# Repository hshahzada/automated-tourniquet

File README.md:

View this project on [CADLAB.io](https://cadlab.io/project/27395). 

# automated-tourniquet
2023/2024 Capstone Design Project for Biomedical Engineering

Created by:

Diana Temelkos dtemelkos@torontomu.ca
https://www.linkedin.com/in/dianatemelkos/

Hassan Khan hassan.a.khan@torontomu.ca
https://www.linkedin.com/in/hassan-khan-5604501a9/

Haashim Shahzada hshahzada@torontomu.ca
https://www.linkedin.com/in/haashimshahzada/

Sayeed Hasan sayeed.hasan@torontomu.ca
https://www.linkedin.com/in/sayeedhasanli/

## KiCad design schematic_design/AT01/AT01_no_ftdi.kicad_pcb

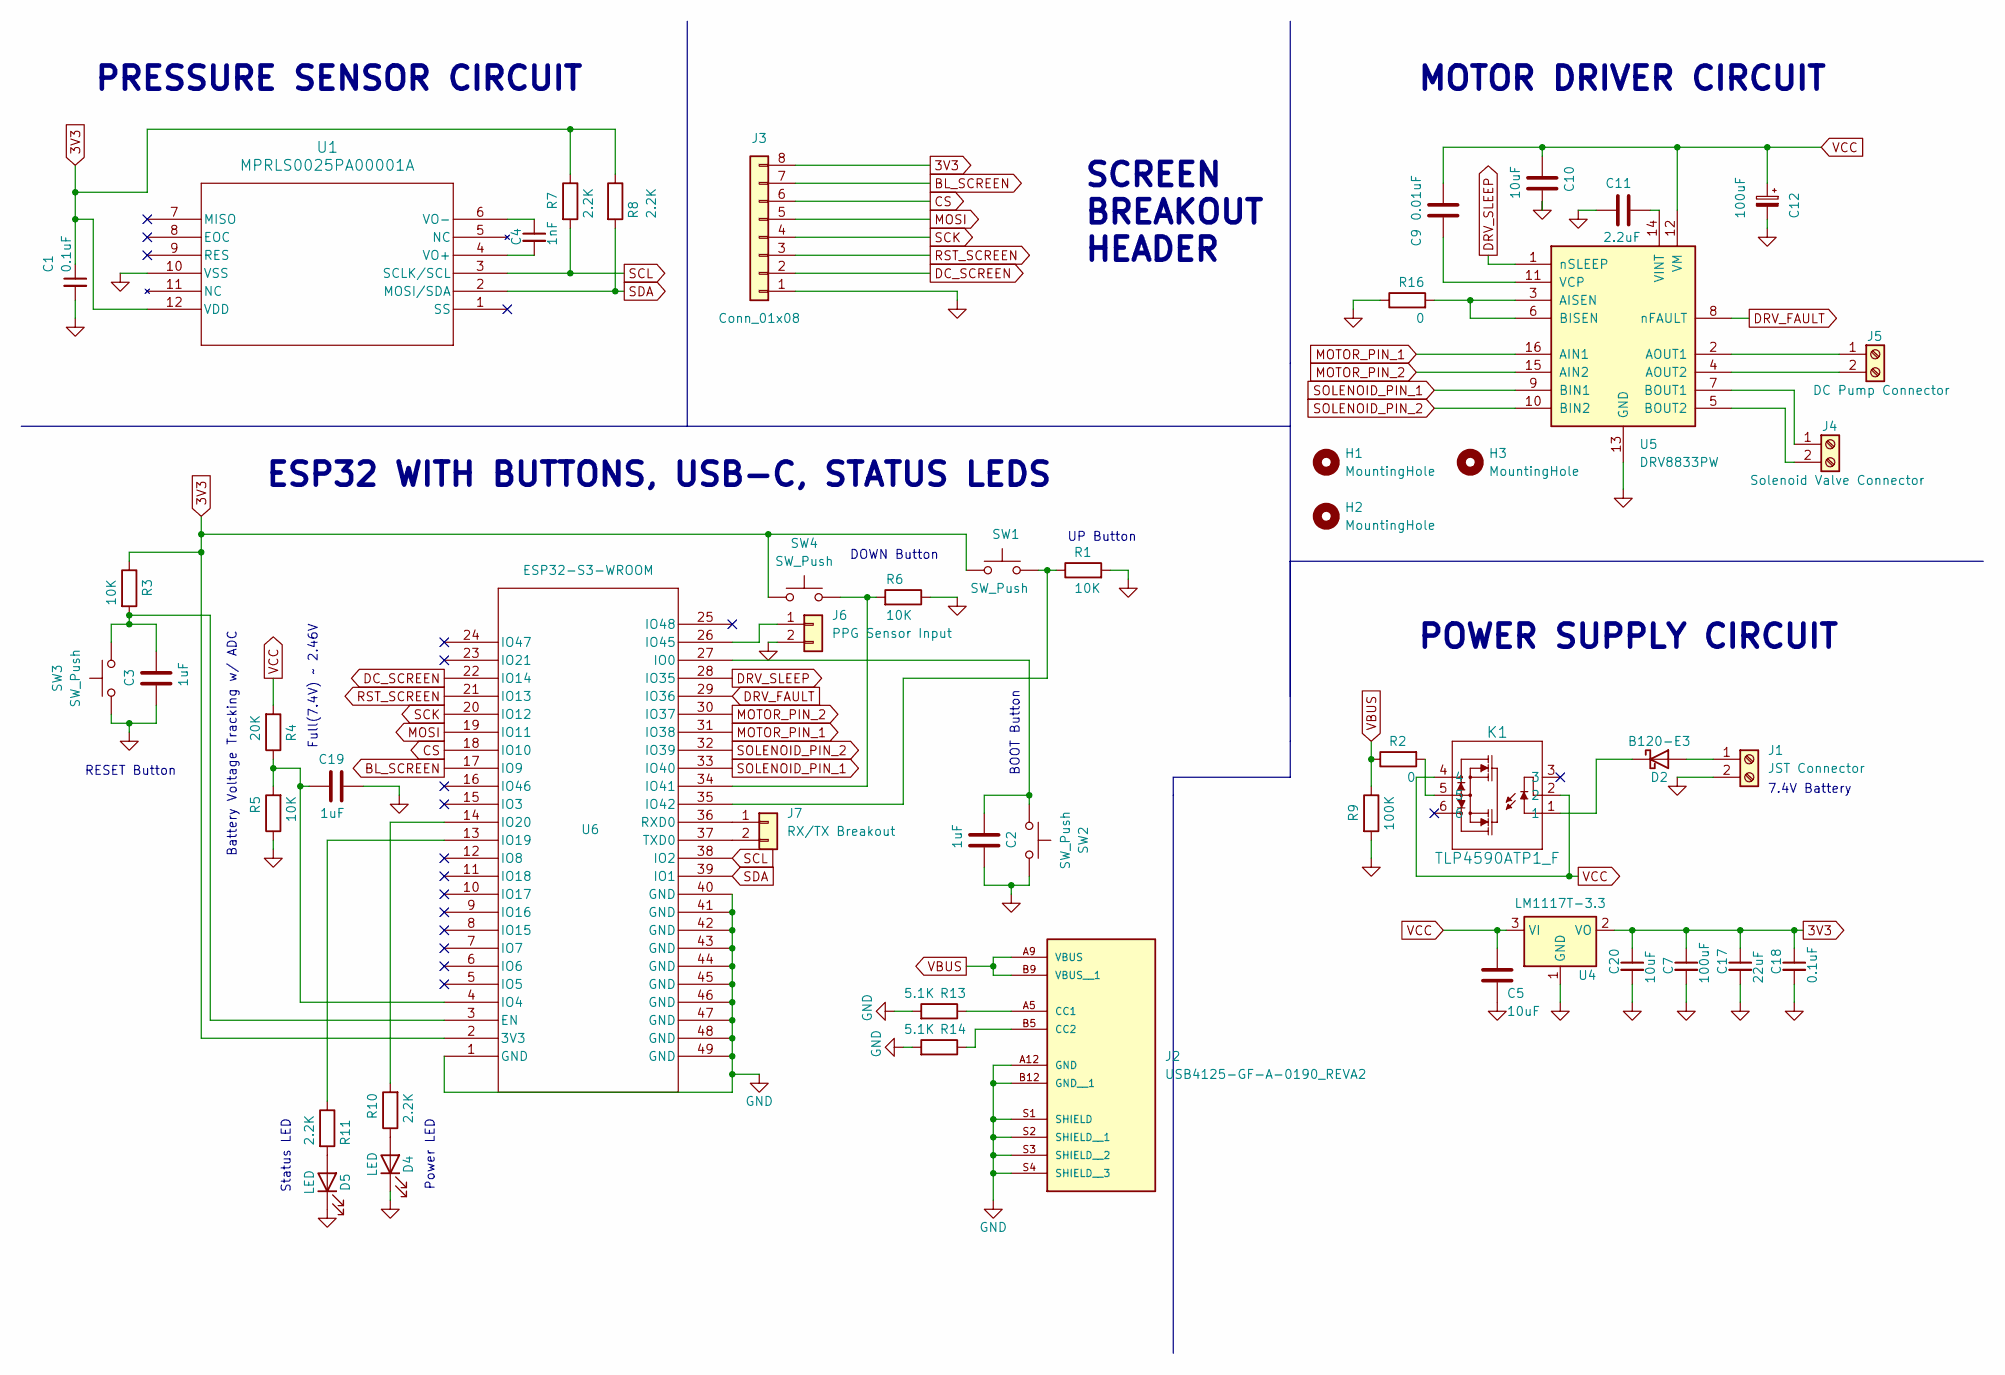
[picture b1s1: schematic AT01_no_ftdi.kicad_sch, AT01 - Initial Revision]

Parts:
C1, C18: 0.1uF; C_0603_1608Metric_Pad1.08x0.95mm_HandSolder
C2, C3, C19: 1uF; C_0603_1608Metric_Pad1.08x0.95mm_HandSolder
C4: 1nF; C_0603_1608Metric_Pad1.08x0.95mm_HandSolder
C5, C10, C20: 10uF; C_0603_1608Metric_Pad1.08x0.95mm_HandSolder
C7: 100uF; C_0805_2012Metric_Pad1.18x1.45mm_HandSolder
C9: 0.01uF; C_0603_1608Metric_Pad1.08x0.95mm_HandSolder
C11: 2.2uF; C_0603_1608Metric_Pad1.08x0.95mm_HandSolder
C12: 100uF; CP_Elec_6.3x5.2
C17: 22uF; C_0603_1608Metric_Pad1.08x0.95mm_HandSolder
D2: B120-E3; D_SMA
D4, D5: LED; LED_D3.0mm
H1, H2, H3: MountingHole; MountingHole_2.2mm_M2_ISO7380
J1: JST Connector; JST_EH_S2B-EH_1x02_P2.50mm_Horizontal
J2: USB4125-GF-A-0190_REVA2; GCT_USB4125-GF-A-0190_REVA2; PARTREV Rev A2
J3: Conn_01x08; PinHeader_1x08_P2.54mm_Vertical
J4: Solenoid Valve Connector; TerminalBlock_4Ucon_1x02_P3.50mm_Horizontal
J5: DC Pump Connector; TerminalBlock_4Ucon_1x02_P3.50mm_Horizontal
J6: PPG Sensor Input; PinHeader_1x02_P2.54mm_Vertical
J7: RX/TX Breakout; PinHeader_1x02_P2.54mm_Vertical
K1: TLP4590ATP1_F; 11-7A801S_TOS
R1, R3, R5, R6: 10K; R_0603_1608Metric_Pad0.98x0.95mm_HandSolder
R2, R16: 0; R_0603_1608Metric_Pad0.98x0.95mm_HandSolder
R4: 20K; R_0603_1608Metric_Pad0.98x0.95mm_HandSolder
R7, R8, R10, R11: 2.2K; R_0603_1608Metric_Pad0.98x0.95mm_HandSolder
R9: 100K; R_0603_1608Metric_Pad0.98x0.95mm_HandSolder
R13, R14: 5.1K; R_0603_1608Metric_Pad0.98x0.95mm_HandSolder
SW1, SW2, SW3, SW4: SW_Push; SW_PUSH_6mm
U1: MPRLS0025PA00001A; MPRLS_HNW
U4: LM1117T-3.3; TO-220-3_Horizontal_TabDown
U5: DRV8833PW; TSSOP-16_4.4x5mm_P0.65mm
U6: ESP32-S3-WROOM; ESP32-S3-WROOM-1U

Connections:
3V3: C1.1, C7.1, C17.1, C18.1, C20.1, J3.8, R3.1, R7.1, R8.1, SW1.1, SW4.1, U1.12 (VDD), U4.2 (VO), U6.2 (3V3)
BL_SCREEN: J3.7, U6.17 (IO9)
CS: J3.6, U6.18 (IO10)
DC_SCREEN: J3.2, U6.22 (IO14)
DRV_FAULT: U5.8 (nFAULT), U6.29 (IO36)
DRV_SLEEP: U5.1 (nSLEEP), U6.28 (IO35)
GND: C1.2, C2.2, C3.2, C5.2, C7.2, C10.1, C11.1, C12.2, C17.2, C18.2, C19.2, C20.2, D4.1 (K), D5.1 (K), J1.2, J2.A12 (GND), J2.B12 (GND__1), J2.S1 (SHIELD), J2.S2 (SHIELD__1), J2.S3 (SHIELD__2), J2.S4 (SHIELD__3), J3.1, J6.2, R1.2, R5.1, R6.1, R9.2, R13.2, R14.2, R16.1, SW2.2, SW3.2, U1.10 (VSS), U4.1 (GND), U5.13 (GND), U6.1 (GND), U6.40 (GND), U6.41 (GND), U6.42 (GND), U6.43 (GND), U6.44 (GND), U6.45 (GND), U6.46 (GND), U6.47 (GND), U6.48 (GND), U6.49 (GND)
MOSI: J3.5, U6.19 (IO11)
MOTOR_PIN_1: U5.16 (AIN1), U6.31 (IO38)
MOTOR_PIN_2: U5.15 (AIN2), U6.30 (IO37)
unnamed: D2.2 (A), J1.1
unnamed: D2.1 (K), K1.1
unnamed: D4.2 (A), R10.1
unnamed: D5.2 (A), R11.2
unnamed: J2.A5 (CC1), R13.1
unnamed: J2.B5 (CC2), R14.1
unnamed: J4.1, U5.7 (BOUT1)
unnamed: J4.2, U5.5 (BOUT2)
unnamed: J5.1, U5.2 (AOUT1)
unnamed: J5.2, U5.4 (AOUT2)
unnamed: J6.1, U6.26 (IO45)
unnamed: J7.1, U6.36 (RXD0)
unnamed: J7.2, U6.37 (TXD0)
unnamed: K1.5, R2.2
unnamed: C4.2, U1.4 (VO+)
unnamed: C4.1, U1.6 (VO-)
unnamed: R16.2, U5.3 (AISEN), U5.6 (BISEN)
unnamed: C9.1, U5.11 (VCP)
unnamed: C11.2, U5.14 (VINT)
unnamed: C3.1, R3.2, SW3.1, U6.3 (EN)
unnamed: C2.1, SW2.1, U6.27 (IO0)
unnamed: C19.1, R4.1, R5.2, U6.4 (IO4)
unnamed: R11.1, U6.13 (IO19)
unnamed: R10.2, U6.14 (IO20)
unnamed: R6.2, SW4.2, U6.34 (IO41)
unnamed: R1.1, SW1.2, U6.35 (IO42)
RST_SCREEN: J3.3, U6.21 (IO13)
SCK: J3.4, U6.20 (IO12)
SCL: R7.2, U1.3 (SCLK/SCL), U6.38 (IO2)
SDA: R8.2, U1.2 (MOSI/SDA), U6.39 (IO1)
SOLENOID_PIN_1: U5.9 (BIN1), U6.33 (IO40)
SOLENOID_PIN_2: U5.10 (BIN2), U6.32 (IO39)
VBUS: J2.A9 (VBUS), J2.B9 (VBUS__1), R2.1, R9.1
VCC: C5.1, C9.2, C10.2, C12.1, K1.2, K1.4, R4.2, U4.3 (VI), U5.12 (VM)

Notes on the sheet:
UP Button
Full(7.4V) ~ 2.46V
PRESSURE SENSOR CIRCUIT
RESET Button
POWER SUPPLY CIRCUIT
7.4V Battery
ESP32 WITH BUTTONS, USB-C, STATUS LEDS
Power LED
SCREEN BREAKOUT HEADER
BOOT Button
MOTOR DRIVER CIRCUIT
DOWN Button
Battery Voltage Tracking w/ ADC
Status LED

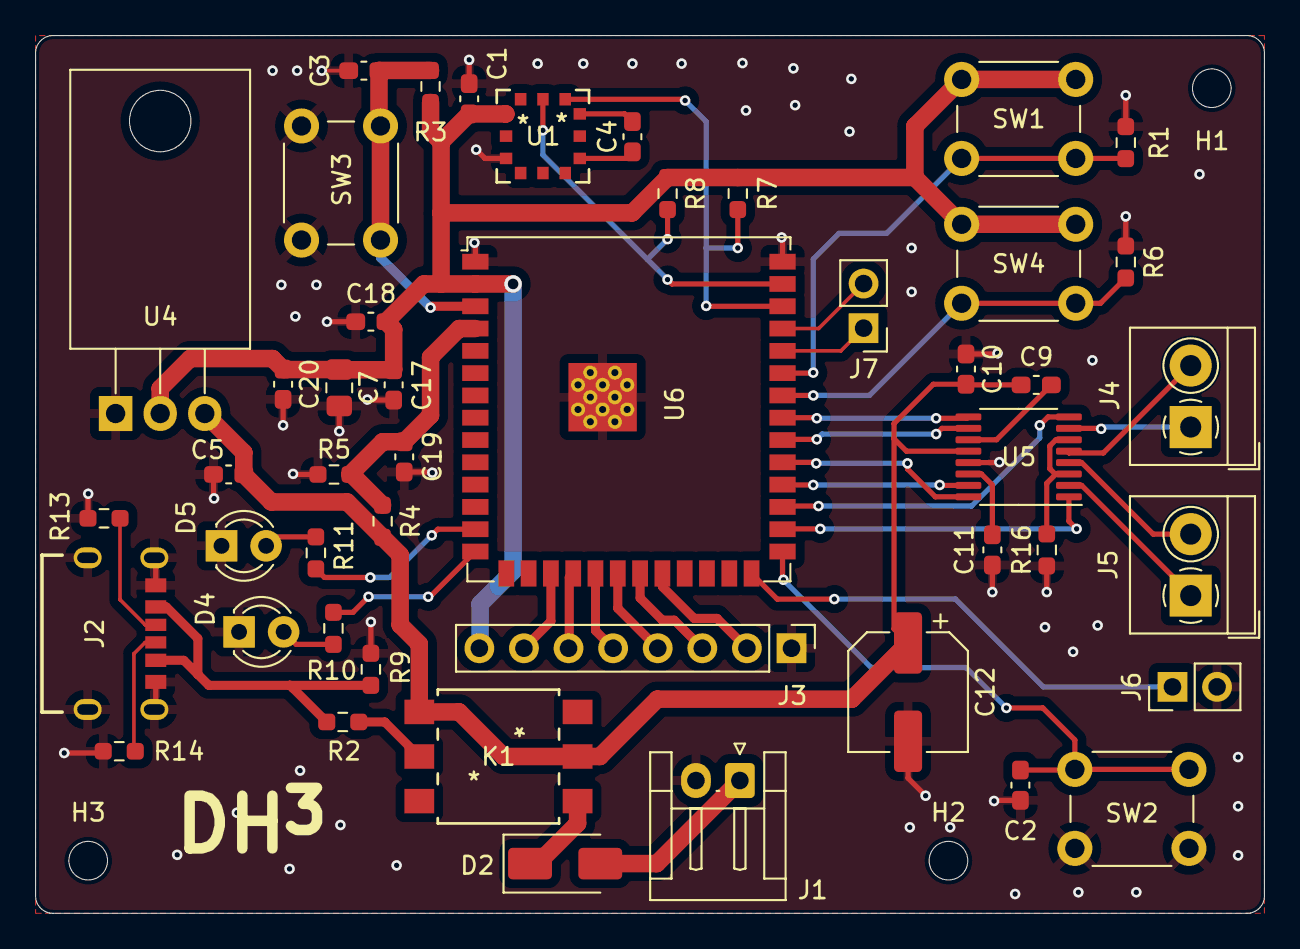
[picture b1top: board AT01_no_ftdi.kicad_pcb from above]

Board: 2 copper layers, 70.0 x 50.0 mm, 50 parts (0 on the bottom side), 44 nets.

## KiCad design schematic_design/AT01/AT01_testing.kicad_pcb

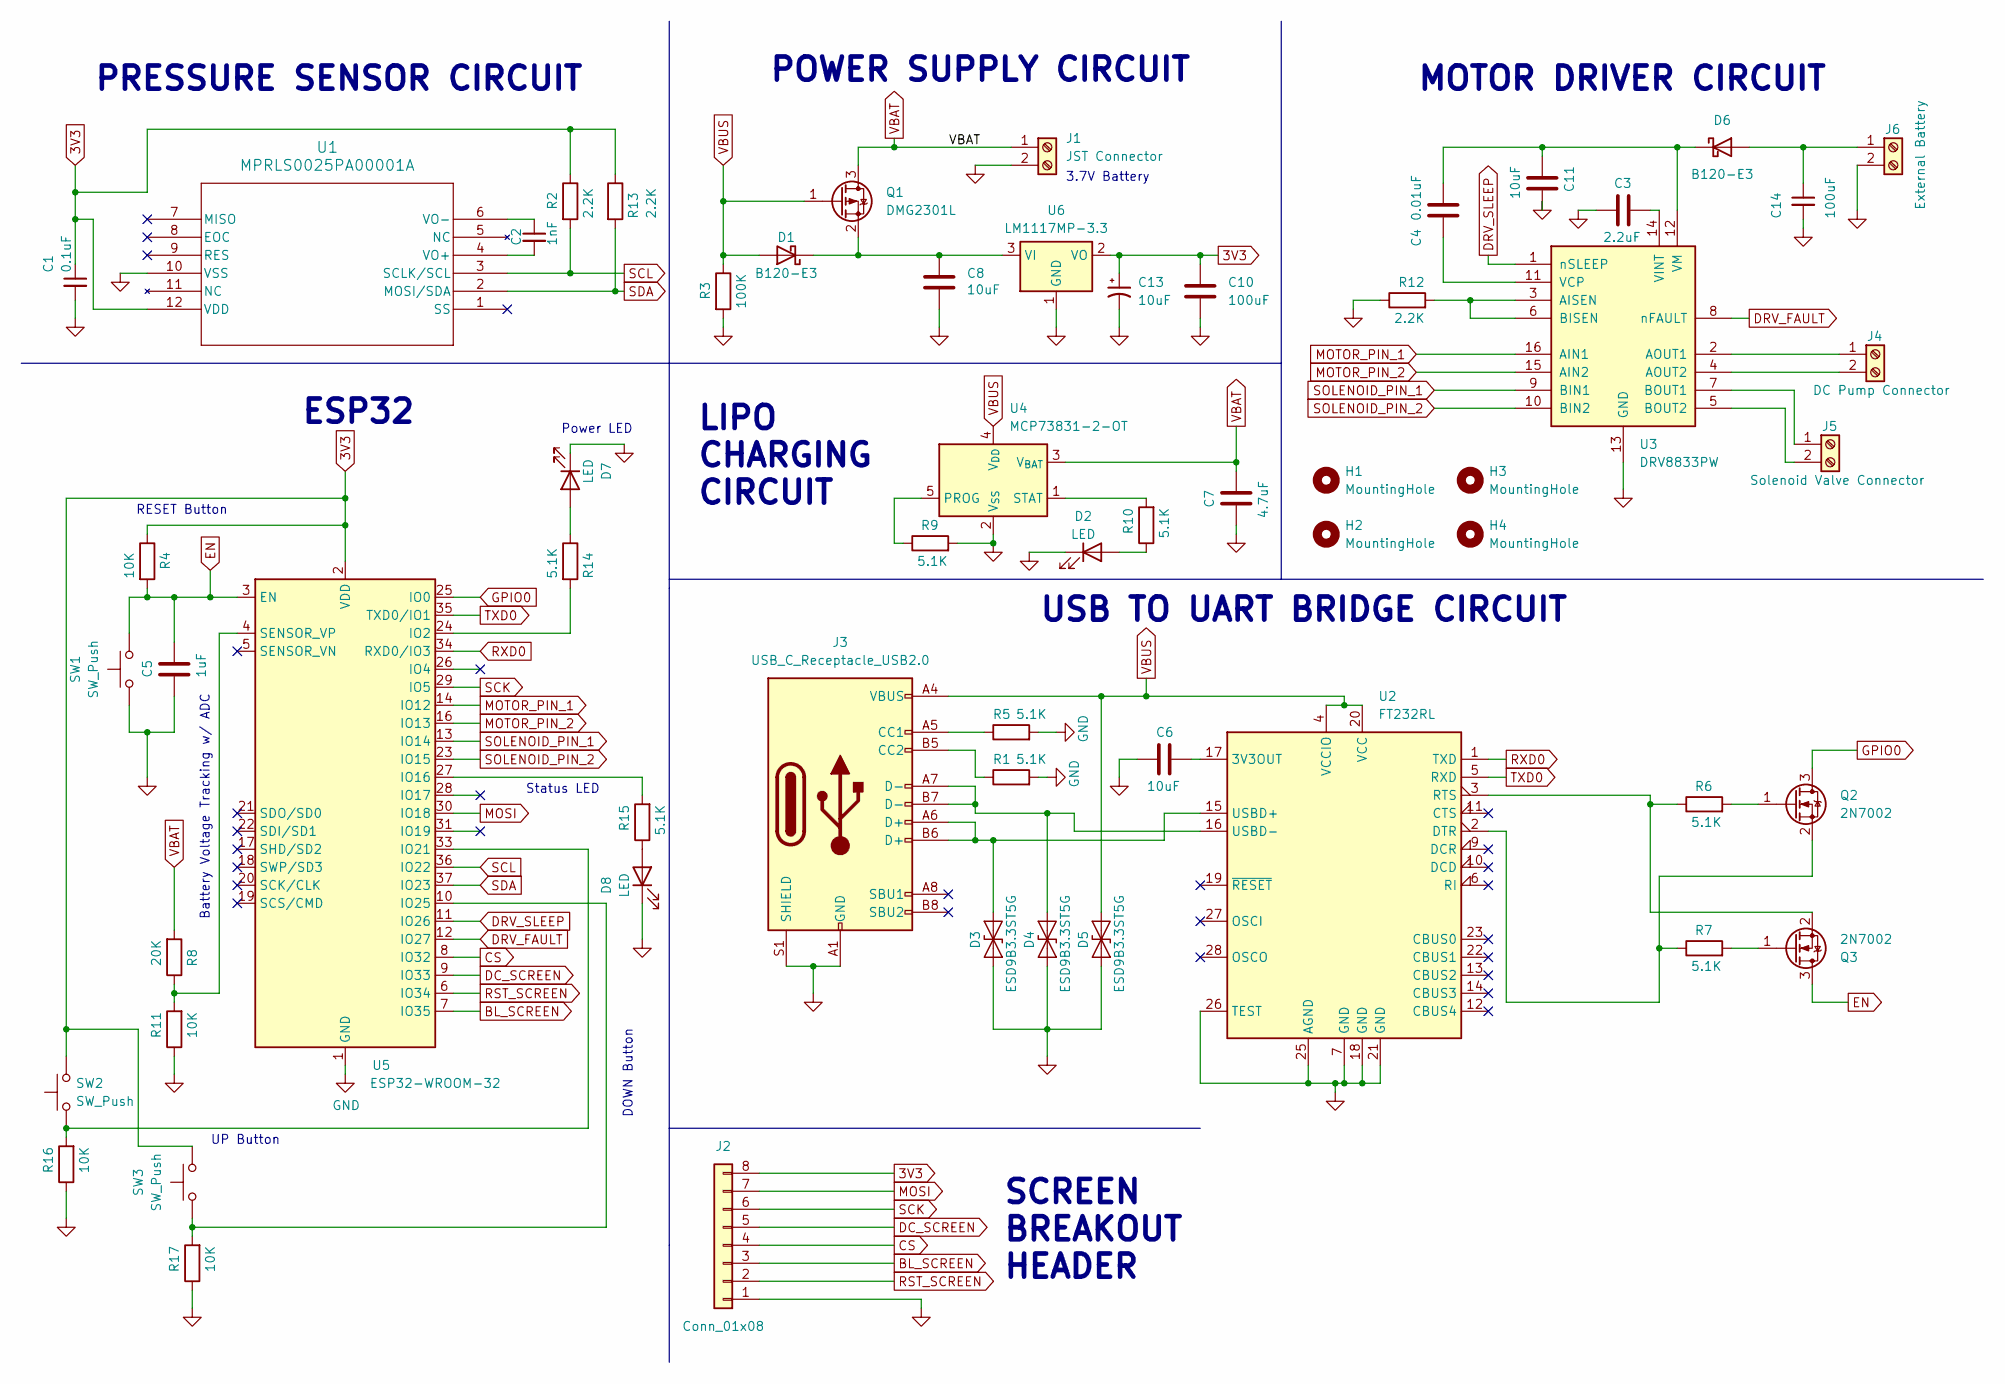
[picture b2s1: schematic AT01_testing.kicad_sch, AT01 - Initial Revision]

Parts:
C1: 0.1uF; C_0402_1005Metric_Pad0.74x0.62mm_HandSolder
C2: 1nF; C_0402_1005Metric_Pad0.74x0.62mm_HandSolder
C3: 2.2uF; C_0402_1005Metric_Pad0.74x0.62mm_HandSolder
C4: 0.01uF; C_0402_1005Metric_Pad0.74x0.62mm_HandSolder
C5: 1uF; C_0402_1005Metric_Pad0.74x0.62mm_HandSolder
C6, C8, C11: 10uF; C_0402_1005Metric_Pad0.74x0.62mm_HandSolder
C7: 4.7uF; C_0402_1005Metric_Pad0.74x0.62mm_HandSolder
C10, C14: 100uF; C_0402_1005Metric_Pad0.74x0.62mm_HandSolder
C13: 10uF; C_1206_3216Metric_Pad1.33x1.80mm_HandSolder
D1, D6: B120-E3; D_SMA
D2, D7, D8: LED; LED_D3.0mm
D3, D4, D5: ESD9B3.3ST5G; D_SOD-923
H1, H2, H3, H4: MountingHole; MountingHole_2.2mm_M2_ISO7380
J1: JST Connector; JST_EH_S2B-EH_1x02_P2.50mm_Horizontal
J2: Conn_01x08; PinHeader_1x08_P1.00mm_Vertical
J3: USB_C_Receptacle_USB2.0; USB_C_Receptacle_HRO_TYPE-C-31-M-12
J4: DC Pump Connector; TerminalBlock_4Ucon_1x02_P3.50mm_Horizontal
J5: Solenoid Valve Connector; TerminalBlock_4Ucon_1x02_P3.50mm_Horizontal
J6: External Battery; TerminalBlock_4Ucon_1x02_P3.50mm_Horizontal
Q1: DMG2301L; SOT-23
Q2, Q3: 2N7002; SOT-23
R1, R5, R6, R7, R9, R10, R14, R15: 5.1K; R_0402_1005Metric_Pad0.72x0.64mm_HandSolder
R2, R12, R13: 2.2K; R_0402_1005Metric_Pad0.72x0.64mm_HandSolder
R3: 100K; R_0402_1005Metric_Pad0.72x0.64mm_HandSolder
R4, R11, R16, R17: 10K; R_0402_1005Metric_Pad0.72x0.64mm_HandSolder
R8: 20K; R_0402_1005Metric_Pad0.72x0.64mm_HandSolder
SW1, SW2, SW3: SW_Push; SW_PUSH_6mm
U1: MPRLS0025PA00001A; MPRLS_HNW
U2: FT232RL; SSOP-28_5.3x10.2mm_P0.65mm
U3: DRV8833PW; TSSOP-16_4.4x5mm_P0.65mm
U4: MCP73831-2-OT; SOT-23-5
U5: ESP32-WROOM-32; ESP32-WROOM-32UE
U6: LM1117MP-3.3; SOT-223-3_TabPin2

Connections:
3V3: C1.1, C10.1, C13.1, J2.8, R2.1, R4.1, R13.1, SW2.1, SW3.1, U1.12 (VDD), U5.2 (VDD), U6.2 (VO)
BL_SCREEN: J2.3, U5.7 (IO35)
CS: J2.4, U5.8 (IO32)
DC_SCREEN: J2.5, U5.9 (IO33)
DRV_FAULT: U3.8 (nFAULT), U5.12 (IO27)
DRV_SLEEP: U3.1 (nSLEEP), U5.11 (IO26)
EN: C5.1, Q3.3 (D), R4.2, SW1.1, U5.3 (EN)
GND: C1.2, C3.1, C5.2, C6.2, C7.1, C8.2, C10.2, C11.1, C13.2, C14.2, D2.1 (K), D3.1 (A1), D4.1 (A1), D5.1 (A1), D7.1 (K), D8.1 (K), J1.2, J2.1, J3.A1 (GND), J3.A12 (GND), J3.B1 (GND), J3.B12 (GND), J3.S1 (SHIELD), J6.2, R1.2, R3.2, R5.2, R9.2, R11.1, R12.1, R16.1, R17.1, SW1.2, U1.10 (VSS), U2.7 (GND), U2.18 (GND), U2.21 (GND), U2.25 (AGND), U2.26 (TEST), U3.13 (GND), U4.2 (V_{SS}), U5.1 (GND), U5.15 (GND), U5.38 (GND), U5.39 (GND), U6.1 (GND)
GPIO0: Q2.3 (D), U5.25 (IO0)
MOSI: J2.7, U5.30 (IO18)
MOTOR_PIN_1: U3.16 (AIN1), U5.14 (IO12)
MOTOR_PIN_2: U3.15 (AIN2), U5.16 (IO13)
unnamed: C8.1, D1.1 (K), Q1.2 (S), U6.3 (VI)
unnamed: D2.2 (A), R10.1
unnamed: D3.2 (A2), J3.A6 (D+), J3.B6 (D+), U2.15 (USBD+)
unnamed: D4.2 (A2), J3.A7 (D-), J3.B7 (D-), U2.16 (USBD-)
unnamed: C14.1, D6.2 (A), J6.1
unnamed: C4.2, C11.2, D6.1 (K), U3.12 (VM)
unnamed: D7.2 (A), R14.1
unnamed: D8.2 (A), R15.1
unnamed: J3.A5 (CC1), R5.1
unnamed: J3.B5 (CC2), R1.1
unnamed: J4.1, U3.2 (AOUT1)
unnamed: J4.2, U3.4 (AOUT2)
unnamed: J5.1, U3.7 (BOUT1)
unnamed: J5.2, U3.5 (BOUT2)
unnamed: Q2.1 (G), R6.2
unnamed: Q2.2 (S), R7.1, U2.2 (DTR)
unnamed: Q3.1 (G), R7.2
unnamed: Q3.2 (S), R6.1, U2.3 (RTS)
unnamed: C2.2, U1.4 (VO+)
unnamed: C2.1, U1.6 (VO-)
unnamed: C6.1, U2.17 (3V3OUT)
unnamed: R12.2, U3.3 (AISEN), U3.6 (BISEN)
unnamed: C4.1, U3.11 (VCP)
unnamed: C3.2, U3.14 (VINT)
unnamed: R9.1, U4.5 (PROG)
unnamed: R10.2, U4.1 (STAT)
unnamed: R14.2, U5.24 (IO2)
unnamed: R15.2, U5.27 (IO16)
unnamed: R16.2, SW2.2, U5.33 (IO21)
unnamed: R17.2, SW3.2, U5.10 (IO25)
unnamed: R8.1, R11.2, U5.4 (SENSOR_VP)
RST_SCREEN: J2.2, U5.6 (IO34)
RXD0: U2.1 (TXD), U5.34 (RXD0/IO3)
SCK: J2.6, U5.29 (IO5)
SCL: R2.2, U1.3 (SCLK/SCL), U5.36 (IO22)
SDA: R13.2, U1.2 (MOSI/SDA), U5.37 (IO23)
SOLENOID_PIN_1: U3.9 (BIN1), U5.13 (IO14)
SOLENOID_PIN_2: U3.10 (BIN2), U5.23 (IO15)
TXD0: U2.5 (RXD), U5.35 (TXD0/IO1)
VBAT: C7.2, J1.1, Q1.3 (D), R8.2, U4.3 (V_{BAT})
VBUS: D1.2 (A), D5.2 (A2), J3.A4 (VBUS), J3.A9 (VBUS), J3.B4 (VBUS), J3.B9 (VBUS), Q1.1 (G), R3.1, U2.4 (VCCIO), U2.20 (VCC), U4.4 (V_{DD})

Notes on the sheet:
LIPO CHARGING CIRCUIT
PRESSURE SENSOR CIRCUIT
RESET Button
Power LED
POWER SUPPLY CIRCUIT
UP Button
3.7V Battery
ESP32
USB TO UART BRIDGE CIRCUIT
SCREEN BREAKOUT HEADER
MOTOR DRIVER CIRCUIT
Status LED
DOWN Button
Battery Voltage Tracking w/ ADC

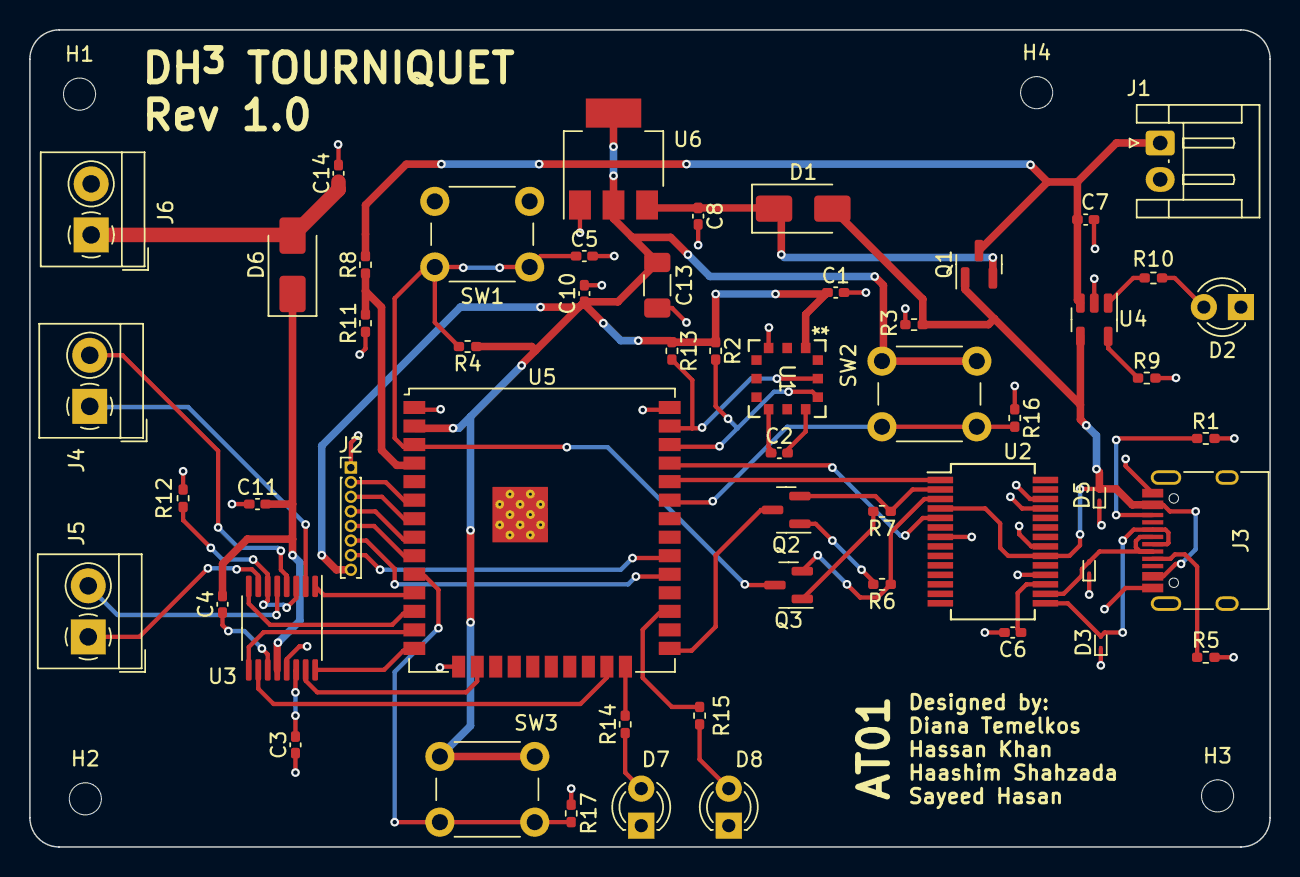
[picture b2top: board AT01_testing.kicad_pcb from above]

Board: 2 copper layers, 85.0 x 56.0 mm, 59 parts (0 on the bottom side), 53 nets.

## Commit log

2023-10-02 Backlink to CADLAB.io has been added.
2023-10-27 Initial Schematic Commit
2023-11-02 Preliminary Schematic
    this schematic is probably wrong, im working on adding battery power at 3.3v regulated and the motor into the schematic. still needs a lot of work
2023-11-02 old preliminary upload didn't work, uploading again
2023-11-03 restructuring directories and adding initial inflation code
2023-11-03 removing old versions of file
2023-11-08 added pressure sensor circuit
2023-11-08 adding power supply circuit to schematic
2023-11-08 adding pressure sensor and diode libs
2023-11-15 adding motor drive schematic
2023-11-16 controlsystem1
    added some control system implementation
2023-11-16 fixing motor driver schematic and adding reset schematic
2023-11-16 completed initial schematic development
2023-12-01 adding libs, cleaning up sch, initial pcb commit
2023-12-19 fixing up labels, gnds, added some protection diodes
2023-12-19 fixing major issue with the LDO
2023-12-21 reddit fixes, adding buttons/leds, restarting pcb layout
2024-01-06 initial layout revision
2024-01-08 DRC fixes
2024-01-11 updated incorrect UART pins
2024-01-11 refreshing codebase to move to platformIO
2024-01-13 adding working code for prototype
2024-01-15 moving gnd panel to back copper, button modifications
2024-01-17 adding working code for sensor, screen, project config settings
2024-01-19 adding board with direct USB-C connection, esp32-s3 based
2024-01-25 added redesigned charging circuit
2024-01-25 adding 2nd page of AT01 sch
2024-01-25 adding library files and datasheets
2024-01-26 PCB redesign for new charging circuit with Espressif recommendations
2024-01-26 adding espressif design review
2024-01-26 adding NC for pin 25, 26
2024-01-27 updated FTDI board
2024-01-27 adding testing PCBs with external batteries
2024-01-28 adding design recommendations from call with Yi
2024-01-29 adding SSR and new ESD protection diodes according to design review
2024-01-29 added random vias on board for better cap control
2024-02-02 added simple control system and button functionality
2024-02-15 final rev1.0 design
2024-03-14 reworking usb c connection
2024-03-22 new code and some schematic work
2024-03-22 removing pressure: psi line to adjust to format
2024-03-22 Added MATLAB Pressure Plotting Script
2024-03-23 Adding interrupt testing code
2024-04-04 adding PID control to main.cpp
2024-04-05 added semi-working menu code
2024-04-05 final working PID implementation
2024-04-05 updating load sharing circuit
2024-04-05 menu and PID integration
2024-04-07 Revised PID and Menu code
2024-04-07 Rev3.0 board commits
2024-04-11 final rev1.0 commit
    switching bicep and thigh occlusion buttons
2024-04-12 adding working LVGL main menu code
2024-04-15 added home page and venepuncture screens
2024-04-22 Completed Main and Occlusion Menus
2024-04-25 fixed actuation screen, arc and labels both work now
2024-04-26 intergrated PID, added ability to change target pressure
2024-04-26 added pressure timer
2024-04-26 added leds
2024-05-07 final code revision
2024-05-07 adding capstone report and poster
2024-05-07 STL readme creation
2024-05-07 adding cad stl files
2024-05-07 changing to assigned student order
